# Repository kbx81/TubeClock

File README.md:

# kbx's Nixie Clock

Nixie Clock project files - PCB and source

For more pictures, see the [gallery](GALLERY.md).

## Another nixie tube clock? Why?

I have to start by giving credit where credit is due. The
[Boldport Club](http://boldport.club), over the last couple of years, has
motivated me to dwell back into the world of electronics, at least as a
hobbyist. Both the kits themselves and the other members in the club are
amazing and helped inspire me to make something...so I began working on this
project. Some inspiration is taken from
[Touchy, BPC Project #7](https://www.boldport.com/products/touchy); this kit
enabled me to learn more about and actually experiment with capacitive touch.
It was clear early on that this would be a nice touch (pun intended) to add to
this project; visually, it is cleaner, it reduces the number of parts and, as a
result, it reduces the cost.

That said, the world probably doesn't need another tube clock. There are
plenty of them--all different shapes and sizes--so why build another one?

Last year, I built this lovely
[binary clock](https://github.com/kbx81/RGBBinaryClock). Some ten-plus years
ago I had built some IN-18 nixie clocks. Earlier this year (2019) one of them
became a little troublesome. I fixed it but, in the interim, became motivated
to build my own. As I already had a wonderful foundation for some clock
hardware, this seemed a natural progression. Overall I'm quite happy with the
results if I may say so myself. :)

_Sooo...another nixie clock? What's special about it?_

**Time & display**
- Shows time, date, and temperature — with a timer/counter mode, too
- 12/24-hour format and °C/°F selectable
- Smooth digit crossfades with configurable animations and effects
- Auto-dims based on ambient light — great for a bedside clock :)

**Time sources** _(all optional — mix and match)_
- GPS sync via a soldered-on LIV3F module or an
  [Adafruit GPS breakout](https://www.adafruit.com/product/746)
- External DS3234 precision RTC
- CR2032 battery or supercapacitor backup to keep time through a power outage

**Control & connectivity**
- Capacitive touch keys
- IR remote control
- [Serial remote protocol](docs/SERIAL_API.md) over UART or USB (CDC-ACM
  virtual serial port)
- Optional Wi-Fi add-on board for wireless control -- I even built an
  [ESPHome external component](https://github.com/kbx81/esphome_external_components/tree/main/components/tube_clock)
- DMX-512 via RS-485 — control each tube individually from a lighting console

**Alarms & audio**
- Up to 8 configurable alarm times with optional display blink
- Hourly binary chime — hear the time from another room!
- RTTTL melody playback
- External alarm trigger via expansion pin header

## What makes it tick?

The brain is an **STM32F072** microcontroller — capable enough on its own, but
with optional add-ons for those who want more:

- **DS3234** — high-accuracy external RTC (also has a built-in temperature sensor)
- **DS1722 / LM74** — dedicated external temperature sensors
- **LIV3F** or **[Adafruit GPS module](https://www.adafruit.com/product/746)**
  for synchronizing time from GPS

The display boards use **HV5622** high-voltage shift registers to drive the
tubes, an **RGB status LED** for at-a-glance info, and a **piezo beeper**
capable of playing RTTTL tunes. An onboard phototransistor handles ambient
light sensing for automatic brightness control.

## How do I get or build one?

In this repository you'll find everything needed to put one together. It is
divided into two major parts: hardware and software (source). The `hardware`
directory contains the [KiCad](http://kicad.org) project files used to create
the printed circuit board. The `src` directory contains the source code needed
to compile and run the application on the microcontroller. It is built on top
of [libopencm3](http://libopencm3.org). Finally, then `bin` directory contains
compiled binary files you may flash directly onto the microcontroller...great
for folks who want to solder something together but don't want to be bothered
with compiling code!

Additional details regarding the hardware and software can be found in the
`README.md` files located in each respective directory.

**That's all for now...thanks for visiting!**

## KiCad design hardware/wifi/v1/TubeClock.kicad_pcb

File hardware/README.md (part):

# kbx's Tube Clock

Tube Clock PCB project files for KiCad (v5)

## How do I get PCBs made for this?

Detailing the process is a bit outside of what I plan to discuss here. There are
 plenty of resources out around the web already that will do a better job of
 explaining this process than I can. That said, there's not much to it -- the
 files you need are here and all you need to do (more or less) is upload them
 to your PCB fabricator of choice and, after a few days, they'll ship them
 to you. I've used [Elecrow](http://elecrow.com) for the prototypes and I can
 assure you that they've turned out fantastic boards given the price.

As the vast majority of the components on this board are surface-mount parts,
 hot air is a fun approach for soldering it all together. If you go this route
 (and especially if you plan to build more than one of them), you'll likely want
 to have a stencil made to help with the placement of solder paste onto the
 board. I ordered a stencil with my board from [Elecrow](http://elecrow.com).

## If I get boards made, how do I build it?

All the components are listed in the KiCad project files here; one will also
 find bill of materials (BoM) files named `TubeClock.BoM.md` or `IN-1x.BoM.md`
 containing these lists. For "unusual" parts (things that aren't resistors or
 capacitors) I've noted a suggested part number that should serve as a point of
 reference to help you find your own.

Before you order parts, be sure to read through the build notes below!

Once you have your boards and parts, there are at least a couple of different
 ways you can build the clock base. Below are build notes.

## Build notes

### Before you begin...

...you need to determine:
1. What will your time source be -- the STM32's RTC, the DS3234, or a GPS
 module? The GPS will provide the best accuracy, followed by the DS3234. That
 said, these ICs will add approximately $10 to $20 USD to the cost of the
 device. If you're purchasing them, double-check those part numbers before
 ordering!
1. What temperature sensor will you use -- the STM32's internal sensor, the
 DS3234's sensor, or a dedicated sensor? The DS1722 or LM74 dedicated sensors
 will provide the best accuracy; however, if one of these ICs is not installed
 but a DS3234 *is* installed, the app will use the DS3234's sensor. Note that,
 while the PCBs have footprints for more than one temperature sensor, only
 **one** of them may be installed at a time. Do not install both!
1. Solder-bridge/jumper settings. These are explained below...but don't forget
 about these!

Once you've settled on the items above, read on (below) for more detail and
 specifics regarding the build.

### Build details

#### GPS:

The clock's application will accept and decode NMEA sentences from an attached
 GPS module. The PCBs will accept a plug-in module from
 [Adafruit](https://www.adafruit.com/product/746) or a Teseo-LIV3F module can
 be installed for a more permanent solution. Testing reveals that both of these
 modules work extremely well and will provide the most accurate time for the
 clock. Note that the LIV3F module will require some additional components to
 operate; several of these parts are 0402-sized (which means that they are very,
 very tiny!) and, as such, are challenging to work with. This approach is best
 for experienced builders with tooling available to work on such tiny parts.

#### External RTC:

The external RTC--the DS3234--adds a level of precision to the clock that is
 likely difficult to achieve with the STM32's internal RTC alone. These RTC ICs
 are designed to drift less than two minutes _per year_. It's possible that your
 STM32 hardware could end up being this accurate, but such accuracy is unlikely.
 Install this IC if you want a clock that is as accurate as is reasonably
 possible without depending on GPS. Note that this IC also has a built-in
 temperature sensor (that's part of how it maintains its precision) that the
 application will use if it is installed and the other external temperature
 sensor (below) is _not_ installed.

If you install a DS3234 on your clock, **do not install** these components:
 - `C23`
 - `R16`

#### External temperature sensors:
**U6 and U7**

A challenge with using the STM32's internal temperature sensor is that the
 sensor typically reads a few degrees higher than the temperature around the
 MCU itself. This is because the die, where the sensor is located, is usually
 just a little bit warmer then the package around it. An easy workaround is to
 just subtract a few degrees from the reading -- hence the calibration item
 you'll find in the application's menu structure. It works, but it requires
 someone to tweak it as each chip is likely to be a little different. Naturally,
 this takes away from its accuracy.

Installing an external temperature sensor is a great solution to this problem.
 The application will prefer an external sensor if one is installed; it first
 prefers one of the dedicated temperature sensors. If not installed, it will try
 to use the sensor integrated into the DS3234, should one be installed. If these
 all fail, it will use the STM32's internal sensor as a last resort.

**IMPORTANT NOTE: the PCBs (all hardware versions) have footprints for two
 external temperature sensor ICs. ONLY INSTALL ONE of them. DO NOT INSTALL
 BOTH.** If you install both, neither of them will work and you may cause damage
 to them or to other ICs on the board.

#### RS-485 transceiver:
**U8**

This part will enable the the second USART in the STM32 MCU to be used to
 communicate on an RS-485 bus. The original intention for this feature was to
 enable the device to receive a DMX-512 signal from an entertainment lighting
 console. With some development, it could also be used (for example) to
 synchronize a number of clocks with each other. This interface is more of a toy
 and has no impact on how the clock itself will function. You'll likely want to
 leave it off of the board unless you have a specific plan to use it for
 something.

#### Infrared (IR) receiver module:
**U4**

If the infrared remote control is not needed, this component may be left off of
 the board.

#### Buzzer/beeper components:
**BZ1, D6, Q6, R29**

If you don't want your clock to be able to make any noise at all, it is safe to
 leave these parts off of your board. It'll be sad, but it'll work just fine.

#### Status LED components:
**LED1, LED2, Q3 through Q5, R23 through R28**

The status LED is not typically used during normal operation, however it can be
 enabled as an AM/PM indicator if/when the clock is set in 12-hour mode. It can
 also provide troubleshooting information if your clock doesn't seem to be
 working. That said, it's not necessary unless you like LEDs as much as I do.

#### Reset/Boot buttons:

The reset and boot buttons are of course not required, but it is convenient if
 you plan to do any development with this platform on your own.

### Other requirements

#### 32.768 kHz crystal installation and connection:

A footprint for a 32.768 kHz crystal exists on the PCB. It is used to drive the
 STM32's internal RTC mechanism. This crystal is particularly important if the
 DS3234 IC is **not** installed; in this case, it must be connected to the MCU
 by creating a solder bridge across the appropriate two pads on `SB2`. Failure
 to do so--and if the DS3234 is not installed--means the clock won't run
 (although things otherwise may seem to work).

If the DS3234 **is** installed, `SB2` may be bridged so as to connect the
 DS323x's 32.768 kHz signal output to the STM32's OSC32 input. This is not
 required but it is recommended so that this MCU input isn't left floating. In
 addition, if `SB2` is bridged in this manner, the 32.768 kHz crystal (and its
 drive capacitors) should **not** be installed.

#### Phototransistor series resistors:
 **Q2, RV2, R7 and R10**

The phototransistor enables the application to determine the amount of ambient
 light around the clock so it can adjust the overall display intensity
 accordingly. There is a variable resistor in series with a fixed resistor which
 allows some manual adjustment over the sensitivity of this mechanism. There is
 also a single fixed resistor in parallel with this configuration. It is not
 necessary to install all of these, however it won't hurt anything if you do.
 If the specified phototransistor is used, a single 100K to 150K resistor
 installed for `R10` will probably work well.

#### Status LED:

If installing a status LED, install only LED1 **or** LED2. Do not install both.

### Solder Bridge Jumpers

#### Pulse-Per-Second (PPS) input selection
**SB1**

This jumper determines which peripheral will provide the pulse-per-second input
 to the processor (and application). This enables more precise refreshing of the
 display and allows the application to operate more efficiently. If neither of
 these peripherals is installed, this jumper is not used.

#### 32.768 kHz Oscillator jumper
**SB2**

This jumper determines if the 32.768 kHz oscillator or the DS3234's 32.768 kHz
 output pin is connected to the STM32's OSC32_IN pin. If a DS3234 is **not**
 installed on the board, it must be bridged so that the crystal's pin is
 connected to the OSC32_IN pin. Otherwise, it's best to bridge it to the
 DS3234's 32.768 kHz output pin. Labels on the PCB indicate which position is
 which.

#### USART 1/USB VBUS jumpers
**SB3, SB4**

These jumpers allow the configuration of which USART1 pin on the MCU is
 connected to the six-pin serial header. Because the processor's USB hardware
 expects USB VBUS on PA9, if you plan to use the USB port, SB4 should be bridged
 and SB3 should be bridged to put PB6 on the on the six-pin header. If you do
 not want/need to use the USB port and wish to flash the MCU via the six-pin
 header, SB4 must be left **open** and SB3 should be bridged to put PA9 on the
 six-pin header.

#### Reset Supervisor jumper
**SB5**

 This jumper determines if the DS3234's reset supervisor output pin is connected
  to the STM32's NRST (not-reset) pin. This should be connected if the DS3234 is
  installed, however it sometimes causes issues with flashing the MCU. If you
  installed a DS3234 and are having difficulty flashing the MCU, try
  disconnecting this jumper until the flashing process is complete. Don't forget
  to reconnect it, though!

#### RS-485 Terminator jumper
**SB6**

Bridge this jumper to connect the terminating resistor across the RS-485
 transceiver's input/output pins. This is useful if the board is at the end of
 a RS-485 link.

#### GPS receive and transmit lines
**SB7, SB8**

Bridge these jumpers to connect the GPS module's receive (Rx) and transmit (Tx)
 lines to the STM32 processor's USART1 interface. These jumpers are provided as
 a convenient way to disconnect the serial data lines in the event that USART1
 must be used for programming or debugging after the board has been built,
 particularly with the LIV3F module.

## Before powering it on for the first time...

WAIT! you didn't plug it in yet, did you? Let's do some pre-flight checks to get
 ready to bring up your board!

It's important that we go over the board with a DMM (or at least a continuity
 tester) and check for any nasty shorts. Solder bridges and poor part placement
 are the typical causes of this and it's not uncommon to have them, particularly
 with so many surface-mount parts. We don't want our brand-new clock to let out
 the magic smoke before we even get to use it, do we? :)

Generally, it will suffice to check a few key areas for shorts. Since these are
 surface-mount ICs, it's not uncommon to have solder bridges between some of the
 pins after you've soldered it all together. Don't worry, we can get away
 without checking _all_ of them, but we _do_ need to check a few. Let's make a
 list so we can check them off:
* **Check for shorts between the output of the LDO and ground.** Put one of your
 DMM probes on the power connector's ground pin and the other on the LDO's
 heatsink (the top fin soldered to the board -- this is its 3.3-volt output). If
 you see they're shorted, you'll have to go hunting for the short. Start by
 checking the power pins around the STM32 processor. All of its Vcc and ground
 pins are right next to each other so this is the best place to look first.
* **Check for shorts on the display pin header.** Note that there are multiple
 ground pins on this header so they will naturally appear to be shorted. It is
 important to check for shorts between the pins that supply the various voltages
 to the display board (3.3, 12, and 170 volts). Shorts between any of these pins
 will be disastrous!
* **Check that the solder bridge "jumpers" are set correctly.** You didn't
 forget to bridge these as appropriate, did you? :) See the "Jumpers" section
 above for information on how they should be set.

Once you've confirmed everything above looks good, it should be reasonably safe
 to proceed to the next step -- flashing the firmware onto the STM32 processor!
 After we do this, we'll be able to more effectively identify any other
 soldering-related issues that could be affecting the clock's operation.

After you power on your board for the first time--and if nothing blows
 up--you'll need to flash the firmware onto the STM32 MCU. Use either the USB
 interface, the SWD connection on P1, or the serial interface on J5. You'll need
 an appropriate adapter and/or cable to do so. You will find the source code and
 flashing instructions in the `src` folder one level up in the repo's hierarchy.
 The `bin` directory contains complied binary files for folks who do not wish to
 compile the source code. With the right tools in hand, this can be done in a
 couple of minutes.

If you're having trouble flashing the MCU, please see the next section.

## Troubleshooting

What's that? You couldn't flash the MCU? Or maybe it isn't working perfectly
 after you flashed the MCU? Uh oh...

As I've built...a few...of these to date, here is a list of common issues I've
 stumbled across as well as some notes on how to fix them.

If you're having trouble flashing the MCU, check these items first:
* If a DS3234 is installed, is the reset supervisor jumper bridged? If so, this
 may be holding the STM32 in a reset state too long and your programmer is
 giving up. Open this jumper and try again.
* If there is no DS3234 installed and/or the jumper is already open, check the
 data lines between the port you're using (six-pin serial, USB, or SWD) and the
 processor. Perhaps there is another nasty solder bridge somewhere that's
 shorting one or more of the lines to Vcc, ground, or another adjacent pin. If
 you're using the USB interface, take a close look at D5 and the physical USB
 port itself, as well. The pins on the USB connector are prone to bridging.

If you flashed the MCU and it's now doing...something...but it doesn't seem
 right, here are some more common symptoms and how to fix them:

* **Status LED blinks orange/off but the tubes are blank or flickering
 erratically.** This is indicative of some soldering problem on the SPI1 pins
 of the MCU or on one or more of the HV5622 drivers. Take a close look at these
 pins and rework them as necessary. Also be sure the socket on the display board
 is seated sufficiently onto the logic board's display pin header.
* **One or more of the touch keys don't work.** Check the 1K resistors that sit
 between the touch keys and the MCU as well as the 47 nF sense capacitors.
 Again, also check the relevant pins on the MCU itself for shorts to adjacent
 pins (this is the most common issue).
* **It keeps making a ticking sound.** There's a problem with one or more of the
 touch keys -- see the item above.
* **The status LED alternates red and yellow.** You did not install a DS3234 (or
 maybe you did and it's not working) and the STM32's RTC/LSE oscillator did not
 start within the expected amount of time. Check that `SB2` is bridged correctly
 and that the 32.768 kHz crystal and its bypass capacitors are installed and
 soldered correctly. Also check that the respective pins on the STM32 processor
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
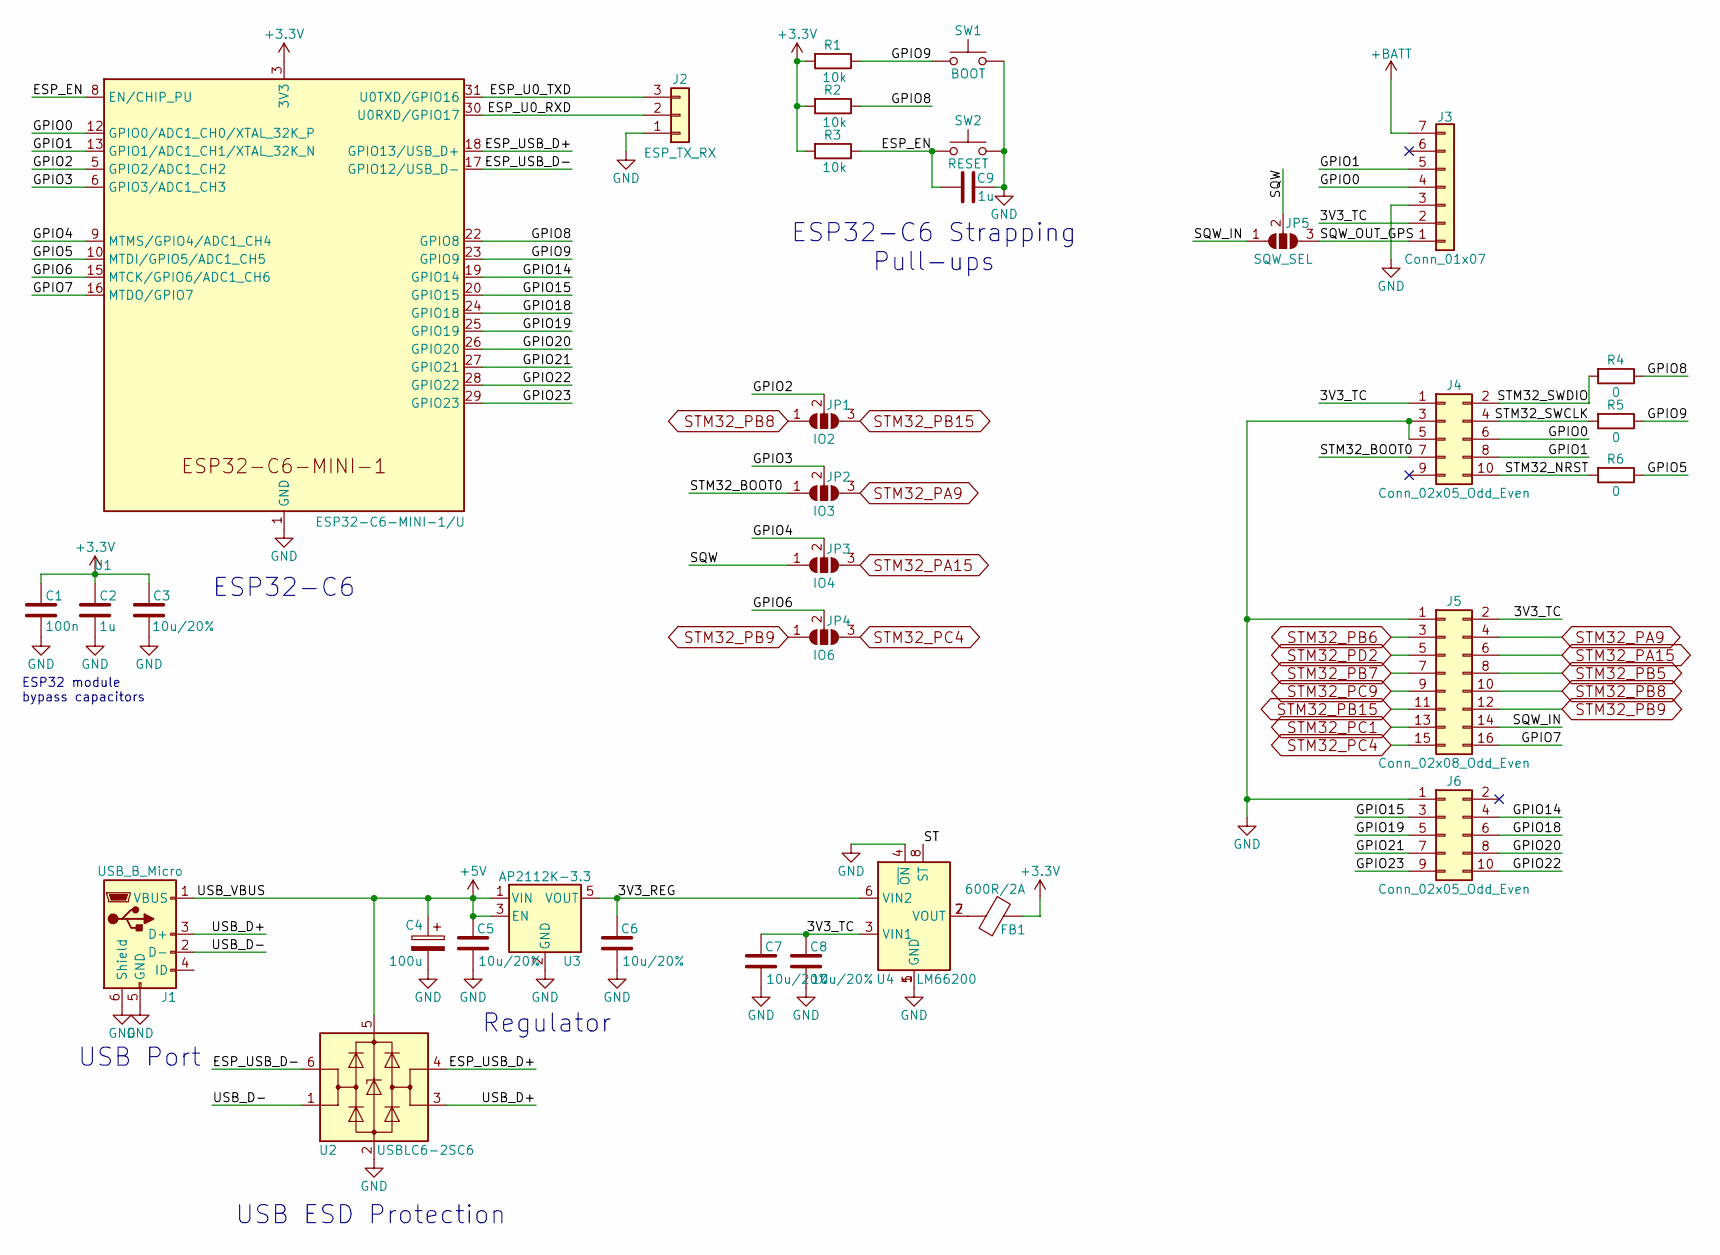
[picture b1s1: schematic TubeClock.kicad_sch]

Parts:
C1: 100n; C_0402_1005Metric; MPN1 CC0402KRX5R6BB104
C2, C9: 1u; C_0402_1005Metric; MPN1 CC0402KRX5R6BB105
C3, C5, C6, C7, C8: 10u/20%; C_0603_1608Metric; MPN1 CC0603MRX5R6BB106
C4: 100u; CP_Elec_5x5.4; MPN1 UWR1A101MCL1GB
FB1: 600R/2A; L_0603_1608Metric; MPN1 MPZ1608S221ATA00
J1: USB_B_Micro; USB_Micro-B_Molex-105017-0001
J2: ESP_TX_RX; PinSocket_1x03_P2.54mm_Vertical
J3: Conn_01x07; PinSocket_1x07_P2.54mm_Vertical
J4: Conn_02x05_Odd_Even; PinHeader_2x05_P1.27mm_Vertical_SMD
J5: Conn_02x08_Odd_Even; PinSocket_2x08_P2.54mm_Vertical
J6: Conn_02x05_Odd_Even; PinSocket_2x05_P2.54mm_Vertical
JP1: IO2; SolderJumper-3_P1.3mm_Open_RoundedPad1.0x1.5mm
JP2: IO3; SolderJumper-3_P1.3mm_Open_RoundedPad1.0x1.5mm
JP3: IO4; SolderJumper-3_P1.3mm_Open_RoundedPad1.0x1.5mm
JP4: IO6; SolderJumper-3_P1.3mm_Open_RoundedPad1.0x1.5mm
JP5: SQW_SEL; SolderJumper-3_P1.3mm_Open_RoundedPad1.0x1.5mm
R1, R2, R3: 10k; R_0402_1005Metric; MPN1 RC0402JR-0710KL
R4, R5, R6: 0; R_0402_1005Metric; MPN1 RC0402JR-070RL
SW1: BOOT; SW_Push_1P1T_NO_CK_KMR2; MPN1 KMR2
SW2: RESET; SW_Push_1P1T_NO_CK_KMR2; MPN1 KMR2
U1: ESP32-C6-MINI-1/U; ESP32-C6-MINI-1; MPN1 ESP32-C6-MINI-1
U2: USBLC6-2SC6; SOT-23-6; MPN1 USBLC6-2SC6
U3: AP2112K-3.3; SOT-23-5; MPN1 AP2112K-3.3TRG1
U4: LM66200; SOT-583-8; MPN1 LM66200

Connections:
+3.3V: C1.1, C2.1, C3.1, FB1.2, R1.2, R2.2, R3.2, U1.3 (3V3)
+5V: C4.1, C5.1, J1.1 (VBUS), U2.5 (VBUS), U3.1 (VIN), U3.3 (EN)
+BATT: J3.7
/3V3_REG: C6.1, U3.5 (VOUT), U4.6 (VIN2)
/3V3_TC: C7.1, C8.1, J3.2, J4.1, J5.2, U4.3 (VIN1)
/ESP_EN: C9.1, R3.1, SW2.1, U1.8 (EN/CHIP_PU)
/ESP_U0_RXD: J2.2, U1.30 (U0RXD/GPIO17)
/ESP_U0_TXD: J2.3, U1.31 (U0TXD/GPIO16)
/ESP_USB_D+: U1.18 (GPIO13/USB_D+), U2.4 (I/O2)
/ESP_USB_D-: U1.17 (GPIO12/USB_D-), U2.6 (I/O1)
/GPIO0: J3.4, J4.6, U1.12 (GPIO0/ADC1_CH0/XTAL_32K_P)
/GPIO1: J3.5, J4.8, U1.13 (GPIO1/ADC1_CH1/XTAL_32K_N)
/GPIO2: JP1.2 (C), U1.5 (GPIO2/ADC1_CH2)
/GPIO3: JP2.2 (C), U1.6 (GPIO3/ADC1_CH3)
/GPIO4: JP3.2 (C), U1.9 (MTMS/GPIO4/ADC1_CH4)
/GPIO5: R6.1, U1.10 (MTDI/GPIO5/ADC1_CH5)
/GPIO6: JP4.2 (C), U1.15 (MTCK/GPIO6/ADC1_CH6)
/GPIO7: J5.16, U1.16 (MTDO/GPIO7)
/GPIO8: R2.1, R4.1, U1.22 (GPIO8)
/GPIO9: R1.1, R5.1, SW1.1, U1.23 (GPIO9)
/GPIO14: J6.4, U1.19 (GPIO14)
/GPIO15: J6.3, U1.20 (GPIO15)
/GPIO18: J6.6, U1.24 (GPIO18)
/GPIO19: J6.5, U1.25 (GPIO19)
/GPIO20: J6.8, U1.26 (GPIO20)
/GPIO21: J6.7, U1.27 (GPIO21)
/GPIO22: J6.10, U1.28 (GPIO22)
/GPIO23: J6.9, U1.29 (GPIO23)
/SQW: JP3.1 (A), JP5.2 (C)
/SQW_IN: J5.14, JP5.1 (A)
/SQW_OUT_GPS: J3.1, JP5.3 (B)
/ST: U4.8 (ST)
/STM32_BOOT0: J4.7, JP2.1 (A)
/STM32_NRST: J4.10, R6.2
/STM32_SWCLK: J4.4, R5.2
/STM32_SWDIO: J4.2, R4.2
/USB_D+: J1.3 (D+), U2.3 (I/O2)
/USB_D-: J1.2 (D-), U2.1 (I/O1)
GND: C1.2, C2.2, C3.2, C4.2, C5.2, C6.2, C7.2, C8.2, C9.2, J1.5 (GND), J1.6 (Shield), J2.1, J3.3, J4.3, J4.5, J5.1, J6.1, SW1.2, SW2.2, U1.1 (GND), U1.2 (GND), U1.11 (GND), U1.14 (GND), U1.36 (GND), U1.37 (GND), U1.38 (GND), U1.39 (GND), U1.40 (GND), U1.41 (GND), U1.42 (GND), U1.43 (GND), U1.44 (GND), U1.45 (GND), U1.46 (GND), U1.47 (GND), U1.48 (GND), U1.49 (GND), U1.50 (GND), U1.51 (GND), U1.52 (GND), U1.53 (GND), U2.2 (GND), U3.2 (GND), U4.1 (GND), U4.4 (~ON), U4.5 (GND)
unnamed: FB1.1, U4.2 (VOUT), U4.7 (VOUT)
STM32_PA9: J5.4, JP2.3 (B)
STM32_PA15: J5.6, JP3.3 (B)
STM32_PB5: J5.8
STM32_PB6: J5.3
STM32_PB7: J5.7
STM32_PB8: J5.10, JP1.1 (A)
STM32_PB9: J5.12, JP4.1 (A)
STM32_PB15: J5.11, JP1.3 (B)
STM32_PC1: J5.13
STM32_PC4: J5.15, JP4.3 (B)
STM32_PC9: J5.9
STM32_PD2: J5.5

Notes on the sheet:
Regulator
ESP32 module bypass capacitors
ESP32-C6
USB Port
ESP32-C6 Strapping Pull-ups
USB ESD Protection

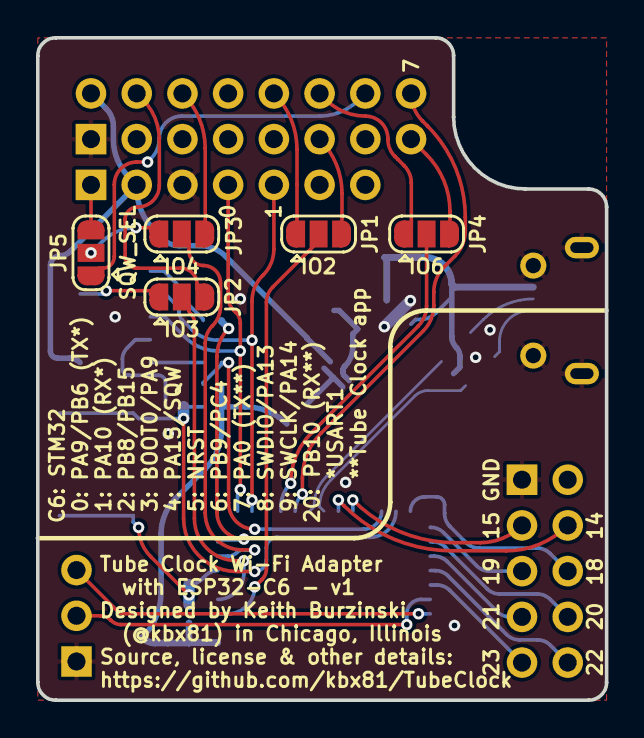
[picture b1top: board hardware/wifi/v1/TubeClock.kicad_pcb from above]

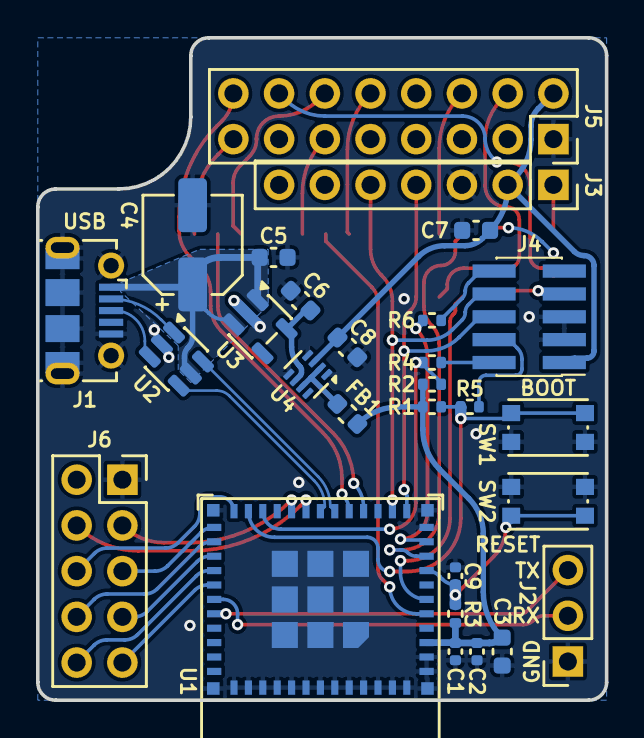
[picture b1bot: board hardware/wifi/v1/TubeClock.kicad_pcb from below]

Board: 2 copper layers, 31.6 x 36.8 mm, 33 parts (28 on the bottom side), 44 nets.

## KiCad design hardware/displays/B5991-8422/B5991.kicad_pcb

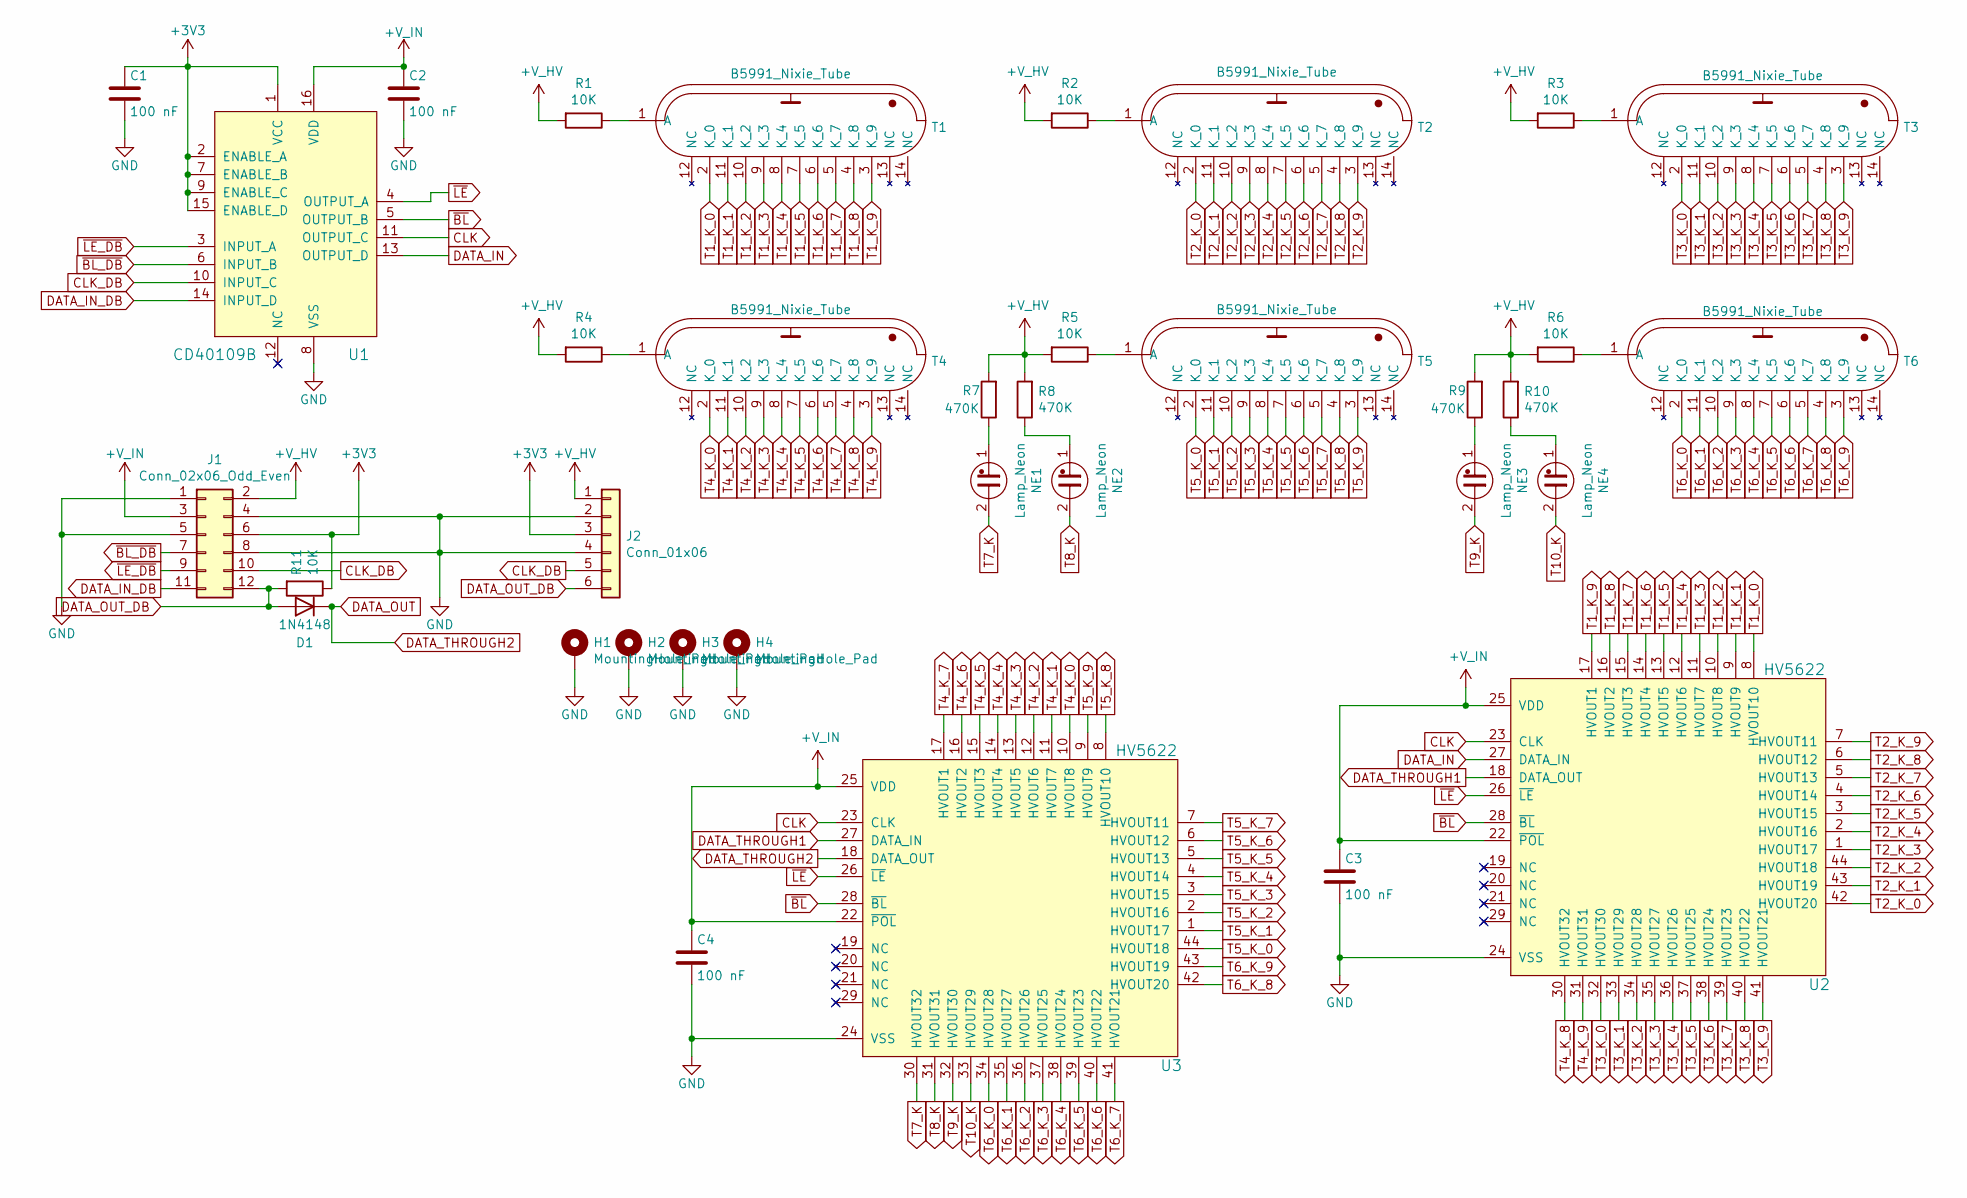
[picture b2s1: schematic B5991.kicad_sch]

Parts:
C1, C2, C3, C4: 100 nF; C_0805_2012Metric
D1: 1N4148; D_SOD-123
H1, H2, H3, H4: MountingHole_Pad; MountingHole_3.2mm_M3_Pad_Via
J1: Conn_02x06_Odd_Even; PinSocket_2x06_P2.54mm_Vertical
J2: Conn_01x06; PinSocket_1x06_P2.54mm_Vertical
NE1, NE2, NE3, NE4: Lamp_Neon; PinSocket_1x02_P2.54mm_Vertical
R1, R2, R3, R4, R5, R6: 10K; R_1206_3216Metric
R7, R8, R9, R10: 470K; R_1206_3216Metric
R11: 10K; R_0805_2012Metric
T1, T2, T3, T4, T5, T6: B5991_Nixie_Tube; Nixie_B5991
U1: CD40109B; SOIC-16W_5.3x10.2mm_P1.27mm
U2, U3: HV5622; PLCC-44_16.6x16.6mm_P1.27mm

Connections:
+3V3: C1.1, J1.6, J2.3, R11.1, U1.1 (VCC), U1.2 (ENABLE_A), U1.7 (ENABLE_B), U1.9 (ENABLE_C), U1.15 (ENABLE_D)
+V_HV: J1.2, J2.1, R1.2, R2.2, R3.2, R4.2, R5.2, R6.2, R7.2, R8.2, R9.2, R10.2
+V_IN: C2.1, C3.1, C4.1, J1.3, U1.16 (VDD), U2.22 (~POL), U2.25 (VDD), U3.22 (~POL), U3.25 (VDD)
CLK: U1.11 (OUTPUT_C), U2.23 (CLK), U3.23 (CLK)
CLK_DB: J1.10, J2.5, U1.10 (INPUT_C)
DATA_IN: U1.13 (OUTPUT_D), U2.27 (DATA_IN)
DATA_IN_DB: J1.11, U1.14 (INPUT_D)
DATA_OUT: D1.1 (K), U3.18 (DATA_OUT)
DATA_OUT_DB: D1.2 (A), J1.12, J2.6, R11.2
DATA_THROUGH1: U2.18 (DATA_OUT), U3.27 (DATA_IN)
GND: C1.2, C2.2, C3.2, C4.2, H1.1, H2.1, H3.1, H4.1, J1.1, J1.4, J1.5, J1.8, J2.2, J2.4, U1.8 (VSS), U2.24 (VSS), U3.24 (VSS)
unnamed: NE1.1, R7.1
unnamed: NE2.1, R8.1
unnamed: NE3.1, R9.1
unnamed: NE4.1, R10.1
unnamed: R1.1, T1.1 (A)
unnamed: R2.1, T2.1 (A)
unnamed: R3.1, T3.1 (A)
unnamed: R4.1, T4.1 (A)
unnamed: R5.1, T5.1 (A)
unnamed: R6.1, T6.1 (A)
T1_K_0: T1.2 (K_0), U2.8 (HVOUT10)
T1_K_1: T1.11 (K_1), U2.9 (HVOUT9)
T1_K_2: T1.10 (K_2), U2.10 (HVOUT8)
T1_K_3: T1.9 (K_3), U2.11 (HVOUT7)
T1_K_4: T1.8 (K_4), U2.12 (HVOUT6)
T1_K_5: T1.7 (K_5), U2.13 (HVOUT5)
T1_K_6: T1.6 (K_6), U2.14 (HVOUT4)
T1_K_7: T1.5 (K_7), U2.15 (HVOUT3)
T1_K_8: T1.4 (K_8), U2.16 (HVOUT2)
T1_K_9: T1.3 (K_9), U2.17 (HVOUT1)
T2_K_0: T2.2 (K_0), U2.42 (HVOUT20)
T2_K_1: T2.11 (K_1), U2.43 (HVOUT19)
T2_K_2: T2.10 (K_2), U2.44 (HVOUT18)
T2_K_3: T2.9 (K_3), U2.1 (HVOUT17)
T2_K_4: T2.8 (K_4), U2.2 (HVOUT16)
T2_K_5: T2.7 (K_5), U2.3 (HVOUT15)
T2_K_6: T2.6 (K_6), U2.4 (HVOUT14)
T2_K_7: T2.5 (K_7), U2.5 (HVOUT13)
T2_K_8: T2.4 (K_8), U2.6 (HVOUT12)
T2_K_9: T2.3 (K_9), U2.7 (HVOUT11)
T3_K_0: T3.2 (K_0), U2.32 (HVOUT30)
T3_K_1: T3.11 (K_1), U2.33 (HVOUT29)
T3_K_2: T3.10 (K_2), U2.34 (HVOUT28)
T3_K_3: T3.9 (K_3), U2.35 (HVOUT27)
T3_K_4: T3.8 (K_4), U2.36 (HVOUT26)
T3_K_5: T3.7 (K_5), U2.37 (HVOUT25)
T3_K_6: T3.6 (K_6), U2.38 (HVOUT24)
T3_K_7: T3.5 (K_7), U2.39 (HVOUT23)
T3_K_8: T3.4 (K_8), U2.40 (HVOUT22)
T3_K_9: T3.3 (K_9), U2.41 (HVOUT21)
T4_K_0: T4.2 (K_0), U3.10 (HVOUT8)
T4_K_1: T4.11 (K_1), U3.11 (HVOUT7)
T4_K_2: T4.10 (K_2), U3.12 (HVOUT6)
T4_K_3: T4.9 (K_3), U3.13 (HVOUT5)
T4_K_4: T4.8 (K_4), U3.14 (HVOUT4)
T4_K_5: T4.7 (K_5), U3.15 (HVOUT3)
T4_K_6: T4.6 (K_6), U3.16 (HVOUT2)
T4_K_7: T4.5 (K_7), U3.17 (HVOUT1)
T4_K_8: T4.4 (K_8), U2.30 (HVOUT32)
T4_K_9: T4.3 (K_9), U2.31 (HVOUT31)
T5_K_0: T5.2 (K_0), U3.44 (HVOUT18)
T5_K_1: T5.11 (K_1), U3.1 (HVOUT17)
T5_K_2: T5.10 (K_2), U3.2 (HVOUT16)
T5_K_3: T5.9 (K_3), U3.3 (HVOUT15)
T5_K_4: T5.8 (K_4), U3.4 (HVOUT14)
T5_K_5: T5.7 (K_5), U3.5 (HVOUT13)
T5_K_6: T5.6 (K_6), U3.6 (HVOUT12)
T5_K_7: T5.5 (K_7), U3.7 (HVOUT11)
T5_K_8: T5.4 (K_8), U3.8 (HVOUT10)
T5_K_9: T5.3 (K_9), U3.9 (HVOUT9)
T6_K_0: T6.2 (K_0), U3.34 (HVOUT28)
T6_K_1: T6.11 (K_1), U3.35 (HVOUT27)
T6_K_2: T6.10 (K_2), U3.36 (HVOUT26)
T6_K_3: T6.9 (K_3), U3.37 (HVOUT25)
T6_K_4: T6.8 (K_4), U3.38 (HVOUT24)
T6_K_5: T6.7 (K_5), U3.39 (HVOUT23)
T6_K_6: T6.6 (K_6), U3.40 (HVOUT22)
T6_K_7: T6.5 (K_7), U3.41 (HVOUT21)
T6_K_8: T6.4 (K_8), U3.42 (HVOUT20)
T6_K_9: T6.3 (K_9), U3.43 (HVOUT19)
T7_K: NE1.2, U3.30 (HVOUT32)
T8_K: NE2.2, U3.31 (HVOUT31)
T9_K: NE3.2, U3.32 (HVOUT30)
T10_K: NE4.2, U3.33 (HVOUT29)
~BL_DB: J1.7, U1.6 (INPUT_B)
~BL: U1.5 (OUTPUT_B), U2.28 (~BL), U3.28 (~BL)
~LE_DB: J1.9, U1.3 (INPUT_A)
~LE: U1.4 (OUTPUT_A), U2.26 (~LE), U3.26 (~LE)

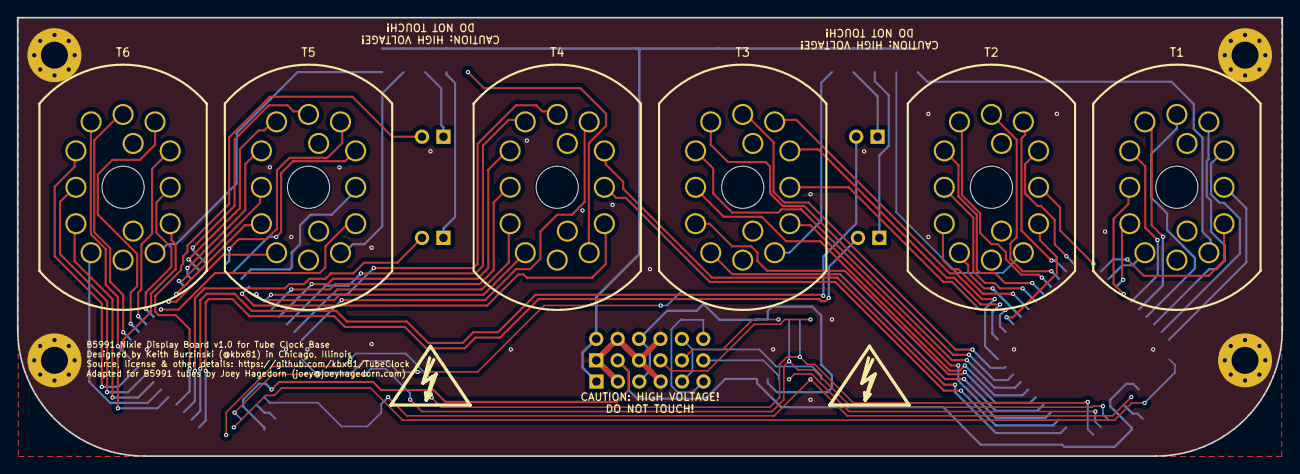
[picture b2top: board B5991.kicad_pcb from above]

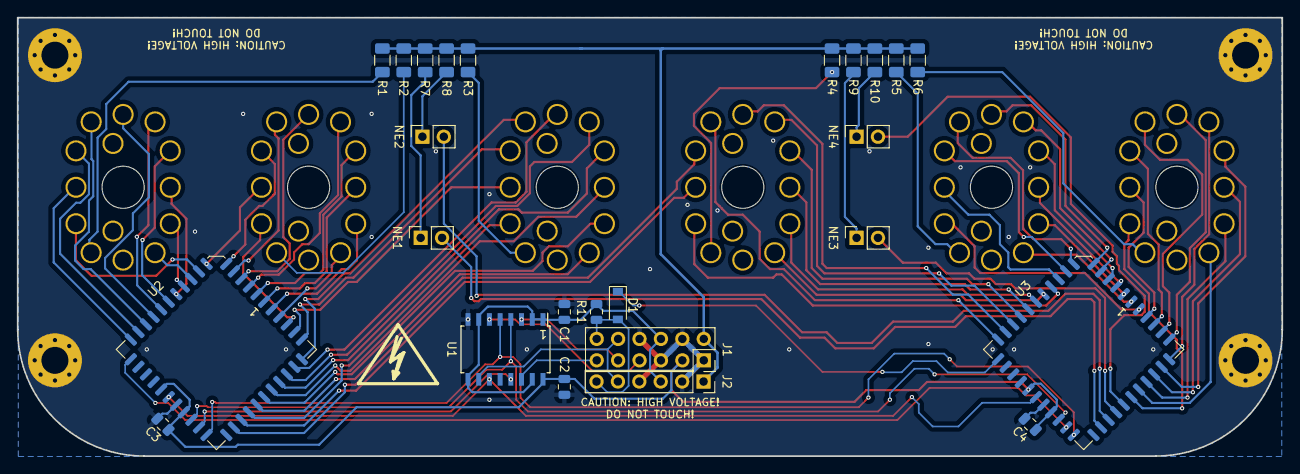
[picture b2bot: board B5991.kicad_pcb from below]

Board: 2 copper layers, 150.0 x 52.0 mm, 35 parts (25 on the bottom side), 89 nets.

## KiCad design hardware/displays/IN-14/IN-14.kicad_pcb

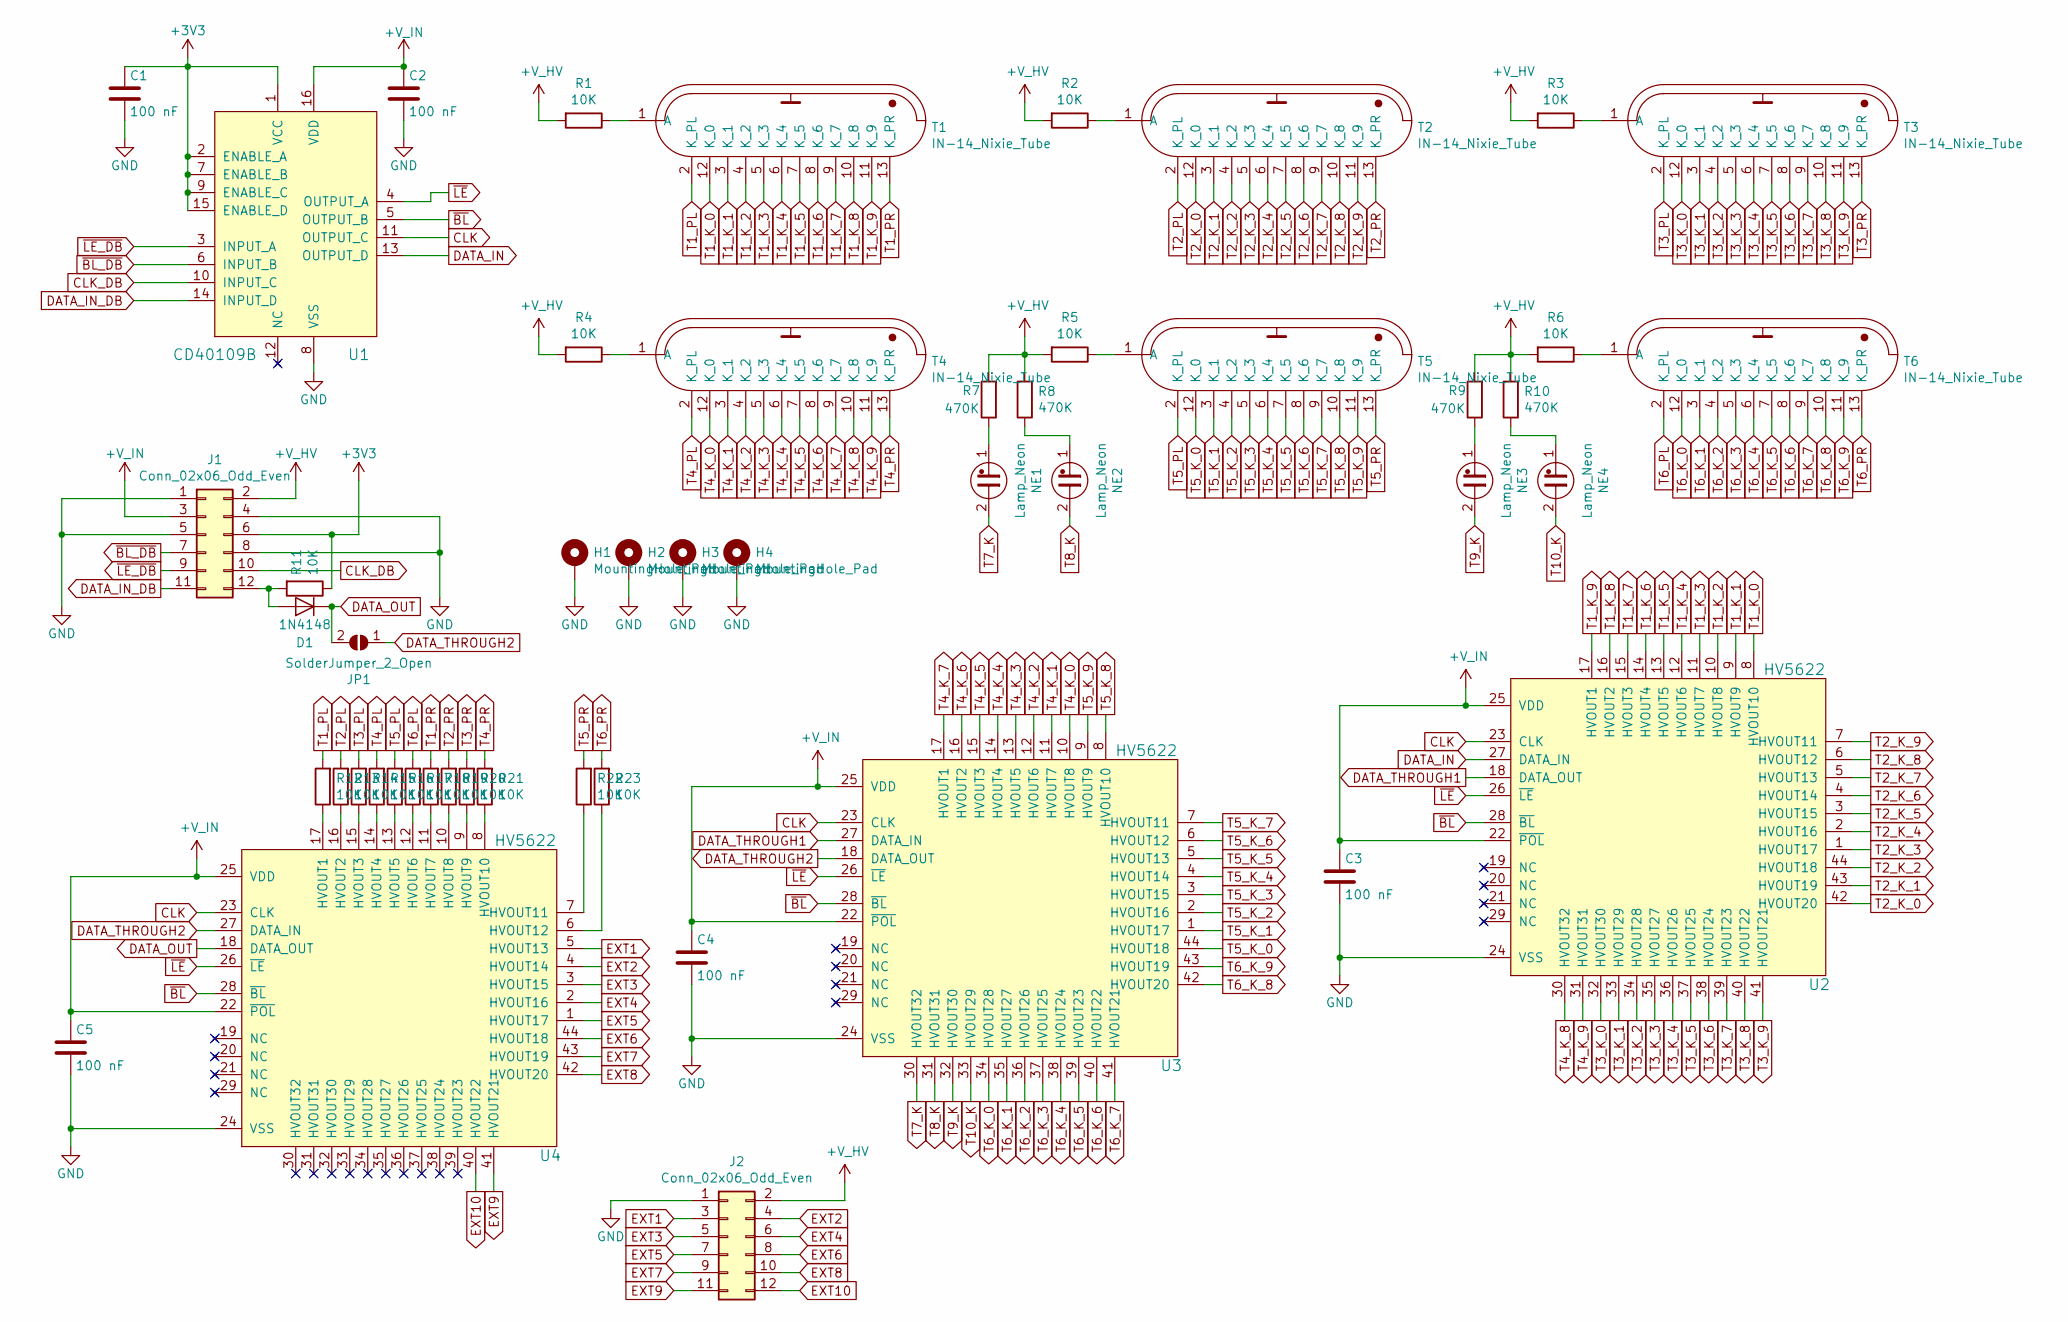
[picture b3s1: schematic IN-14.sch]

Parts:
C1, C2, C3, C4, C5: 100 nF; C_0805_2012Metric
D1: 1N4148; D_SOD-123
H1, H2, H3, H4: MountingHole_Pad; MountingHole_3.2mm_M3_Pad_Via
J1: Conn_02x06_Odd_Even; PinSocket_2x06_P2.54mm_Vertical
J2: Conn_02x06_Odd_Even; PinHeader_2x06_P2.54mm_Vertical
JP1: SolderJumper_2_Open; SolderJumper-2_P1.3mm_Open_Pad1.0x1.5mm
NE1, NE2, NE3, NE4: Lamp_Neon; PinHeader_1x02_P2.54mm_Vertical
R1, R2, R3, R4, R5, R6: 10K; R_1206_3216Metric
R7, R8, R9, R10: 470K; R_1206_3216Metric
R11, R12, R13, R14, R15, R16, R17, R18, R19, R20, R21, R22, R23: 10K; R_0805_2012Metric
T1, T2, T3, T4, T5, T6: IN-14_Nixie_Tube; Nixie_IN-14
U1: CD40109B; SOIC-16W_5.3x10.2mm_P1.27mm
U2, U3, U4: HV5622; PLCC-44_16.6x16.6mm_P1.27mm

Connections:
+3V3: C1.1, J1.6, R11.1, U1.1 (VCC), U1.2 (ENABLE_A), U1.7 (ENABLE_B), U1.9 (ENABLE_C), U1.15 (ENABLE_D)
+V_HV: J1.2, J2.2, R1.2, R2.2, R3.2, R4.2, R5.2, R6.2, R7.2, R8.2, R9.2, R10.2
+V_IN: C2.1, C3.1, C4.1, C5.1, J1.3, U1.16 (VDD), U2.22 (~POL~), U2.25 (VDD), U3.22 (~POL~), U3.25 (VDD), U4.22 (~POL~), U4.25 (VDD)
CLK: U1.11 (OUTPUT_C), U2.23 (CLK), U3.23 (CLK), U4.23 (CLK)
CLK_DB: J1.10, U1.10 (INPUT_C)
DATA_IN: U1.13 (OUTPUT_D), U2.27 (DATA_IN)
DATA_IN_DB: J1.11, U1.14 (INPUT_D)
DATA_OUT: D1.1 (K), JP1.2 (B), U4.18 (DATA_OUT)
DATA_THROUGH1: U2.18 (DATA_OUT), U3.27 (DATA_IN)
DATA_THROUGH2: JP1.1 (A), U3.18 (DATA_OUT), U4.27 (DATA_IN)
EXT1: J2.3, U4.5 (HVOUT13)
EXT2: J2.4, U4.4 (HVOUT14)
EXT3: J2.5, U4.3 (HVOUT15)
EXT4: J2.6, U4.2 (HVOUT16)
EXT5: J2.7, U4.1 (HVOUT17)
EXT6: J2.8, U4.44 (HVOUT18)
EXT7: J2.9, U4.43 (HVOUT19)
EXT8: J2.10, U4.42 (HVOUT20)
EXT9: J2.11, U4.41 (HVOUT21)
EXT10: J2.12, U4.40 (HVOUT22)
GND: C1.2, C2.2, C3.2, C4.2, C5.2, H1.1, H2.1, H3.1, H4.1, J1.1, J1.4, J1.5, J1.8, J2.1, U1.8 (VSS), U2.24 (VSS), U3.24 (VSS), U4.24 (VSS)
unnamed: D1.2 (A), J1.12, R11.2
unnamed: NE1.1, R7.1
unnamed: NE2.1, R8.1
unnamed: NE3.1, R9.1
unnamed: NE4.1, R10.1
unnamed: R1.1, T1.1 (A)
unnamed: R2.1, T2.1 (A)
unnamed: R3.1, T3.1 (A)
unnamed: R4.1, T4.1 (A)
unnamed: R5.1, T5.1 (A)
unnamed: R6.1, T6.1 (A)
unnamed: R12.1, U4.17 (HVOUT1)
unnamed: R13.1, U4.16 (HVOUT2)
unnamed: R14.1, U4.15 (HVOUT3)
unnamed: R15.1, U4.14 (HVOUT4)
unnamed: R16.1, U4.13 (HVOUT5)
unnamed: R17.1, U4.12 (HVOUT6)
unnamed: R18.1, U4.11 (HVOUT7)
unnamed: R19.1, U4.10 (HVOUT8)
unnamed: R20.1, U4.9 (HVOUT9)
unnamed: R21.1, U4.8 (HVOUT10)
unnamed: R22.1, U4.7 (HVOUT11)
unnamed: R23.1, U4.6 (HVOUT12)
T1_K_0: T1.12 (K_0), U2.8 (HVOUT10)
T1_K_1: T1.3 (K_1), U2.9 (HVOUT9)
T1_K_2: T1.4 (K_2), U2.10 (HVOUT8)
T1_K_3: T1.5 (K_3), U2.11 (HVOUT7)
T1_K_4: T1.6 (K_4), U2.12 (HVOUT6)
T1_K_5: T1.7 (K_5), U2.13 (HVOUT5)
T1_K_6: T1.8 (K_6), U2.14 (HVOUT4)
T1_K_7: T1.9 (K_7), U2.15 (HVOUT3)
T1_K_8: T1.10 (K_8), U2.16 (HVOUT2)
T1_K_9: T1.11 (K_9), U2.17 (HVOUT1)
T1_PL: R12.2, T1.2 (K_PL)
T1_PR: R18.2, T1.13 (K_PR)
T2_K_0: T2.12 (K_0), U2.42 (HVOUT20)
T2_K_1: T2.3 (K_1), U2.43 (HVOUT19)
T2_K_2: T2.4 (K_2), U2.44 (HVOUT18)
T2_K_3: T2.5 (K_3), U2.1 (HVOUT17)
T2_K_4: T2.6 (K_4), U2.2 (HVOUT16)
T2_K_5: T2.7 (K_5), U2.3 (HVOUT15)
T2_K_6: T2.8 (K_6), U2.4 (HVOUT14)
T2_K_7: T2.9 (K_7), U2.5 (HVOUT13)
T2_K_8: T2.10 (K_8), U2.6 (HVOUT12)
T2_K_9: T2.11 (K_9), U2.7 (HVOUT11)
T2_PL: R13.2, T2.2 (K_PL)
T2_PR: R19.2, T2.13 (K_PR)
T3_K_0: T3.12 (K_0), U2.32 (HVOUT30)
T3_K_1: T3.3 (K_1), U2.33 (HVOUT29)
T3_K_2: T3.4 (K_2), U2.34 (HVOUT28)
T3_K_3: T3.5 (K_3), U2.35 (HVOUT27)
T3_K_4: T3.6 (K_4), U2.36 (HVOUT26)
T3_K_5: T3.7 (K_5), U2.37 (HVOUT25)
T3_K_6: T3.8 (K_6), U2.38 (HVOUT24)
T3_K_7: T3.9 (K_7), U2.39 (HVOUT23)
T3_K_8: T3.10 (K_8), U2.40 (HVOUT22)
T3_K_9: T3.11 (K_9), U2.41 (HVOUT21)
T3_PL: R14.2, T3.2 (K_PL)
T3_PR: R20.2, T3.13 (K_PR)
T4_K_0: T4.12 (K_0), U3.10 (HVOUT8)
T4_K_1: T4.3 (K_1), U3.11 (HVOUT7)
T4_K_2: T4.4 (K_2), U3.12 (HVOUT6)
T4_K_3: T4.5 (K_3), U3.13 (HVOUT5)
T4_K_4: T4.6 (K_4), U3.14 (HVOUT4)
T4_K_5: T4.7 (K_5), U3.15 (HVOUT3)
T4_K_6: T4.8 (K_6), U3.16 (HVOUT2)
T4_K_7: T4.9 (K_7), U3.17 (HVOUT1)
T4_K_8: T4.10 (K_8), U2.30 (HVOUT32)
T4_K_9: T4.11 (K_9), U2.31 (HVOUT31)
T4_PL: R15.2, T4.2 (K_PL)
T4_PR: R21.2, T4.13 (K_PR)
T5_K_0: T5.12 (K_0), U3.44 (HVOUT18)
T5_K_1: T5.3 (K_1), U3.1 (HVOUT17)
T5_K_2: T5.4 (K_2), U3.2 (HVOUT16)
T5_K_3: T5.5 (K_3), U3.3 (HVOUT15)
T5_K_4: T5.6 (K_4), U3.4 (HVOUT14)
T5_K_5: T5.7 (K_5), U3.5 (HVOUT13)
T5_K_6: T5.8 (K_6), U3.6 (HVOUT12)
T5_K_7: T5.9 (K_7), U3.7 (HVOUT11)
T5_K_8: T5.10 (K_8), U3.8 (HVOUT10)
T5_K_9: T5.11 (K_9), U3.9 (HVOUT9)
T5_PL: R16.2, T5.2 (K_PL)
T5_PR: R22.2, T5.13 (K_PR)
T6_K_0: T6.12 (K_0), U3.34 (HVOUT28)
T6_K_1: T6.3 (K_1), U3.35 (HVOUT27)
T6_K_2: T6.4 (K_2), U3.36 (HVOUT26)
T6_K_3: T6.5 (K_3), U3.37 (HVOUT25)
T6_K_4: T6.6 (K_4), U3.38 (HVOUT24)
T6_K_5: T6.7 (K_5), U3.39 (HVOUT23)
T6_K_6: T6.8 (K_6), U3.40 (HVOUT22)
T6_K_7: T6.9 (K_7), U3.41 (HVOUT21)
T6_K_8: T6.10 (K_8), U3.42 (HVOUT20)
T6_K_9: T6.11 (K_9), U3.43 (HVOUT19)
T6_PL: R17.2, T6.2 (K_PL)
T6_PR: R23.2, T6.13 (K_PR)
T7_K: NE1.2, U3.30 (HVOUT32)
T8_K: NE2.2, U3.31 (HVOUT31)
T9_K: NE3.2, U3.32 (HVOUT30)
T10_K: NE4.2, U3.33 (HVOUT29)
~BL_DB~: J1.7, U1.6 (INPUT_B)
~BL~: U1.5 (OUTPUT_B), U2.28 (~BL~), U3.28 (~BL~), U4.28 (~BL~)
~LE_DB~: J1.9, U1.3 (INPUT_A)
~LE~: U1.4 (OUTPUT_A), U2.26 (~LE~), U3.26 (~LE~), U4.26 (~LE~)

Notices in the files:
hardware/README.md:
Legal stuff and License:
The circuit schematics and PCBs found here are licensed under the
[Creative Commons Attribution-ShareAlike 4.0 International License](http://creativecommons.org/licenses/by-sa/4.0/).
_Happy building!_
